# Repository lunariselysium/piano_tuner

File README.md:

# PianoTuner Legacy Prototype

Status:
Archived

This repository contains early prototype implementation
developed during the initial research phase.

Current commercial development has migrated to:
Melspectrum tech organization private repositories.

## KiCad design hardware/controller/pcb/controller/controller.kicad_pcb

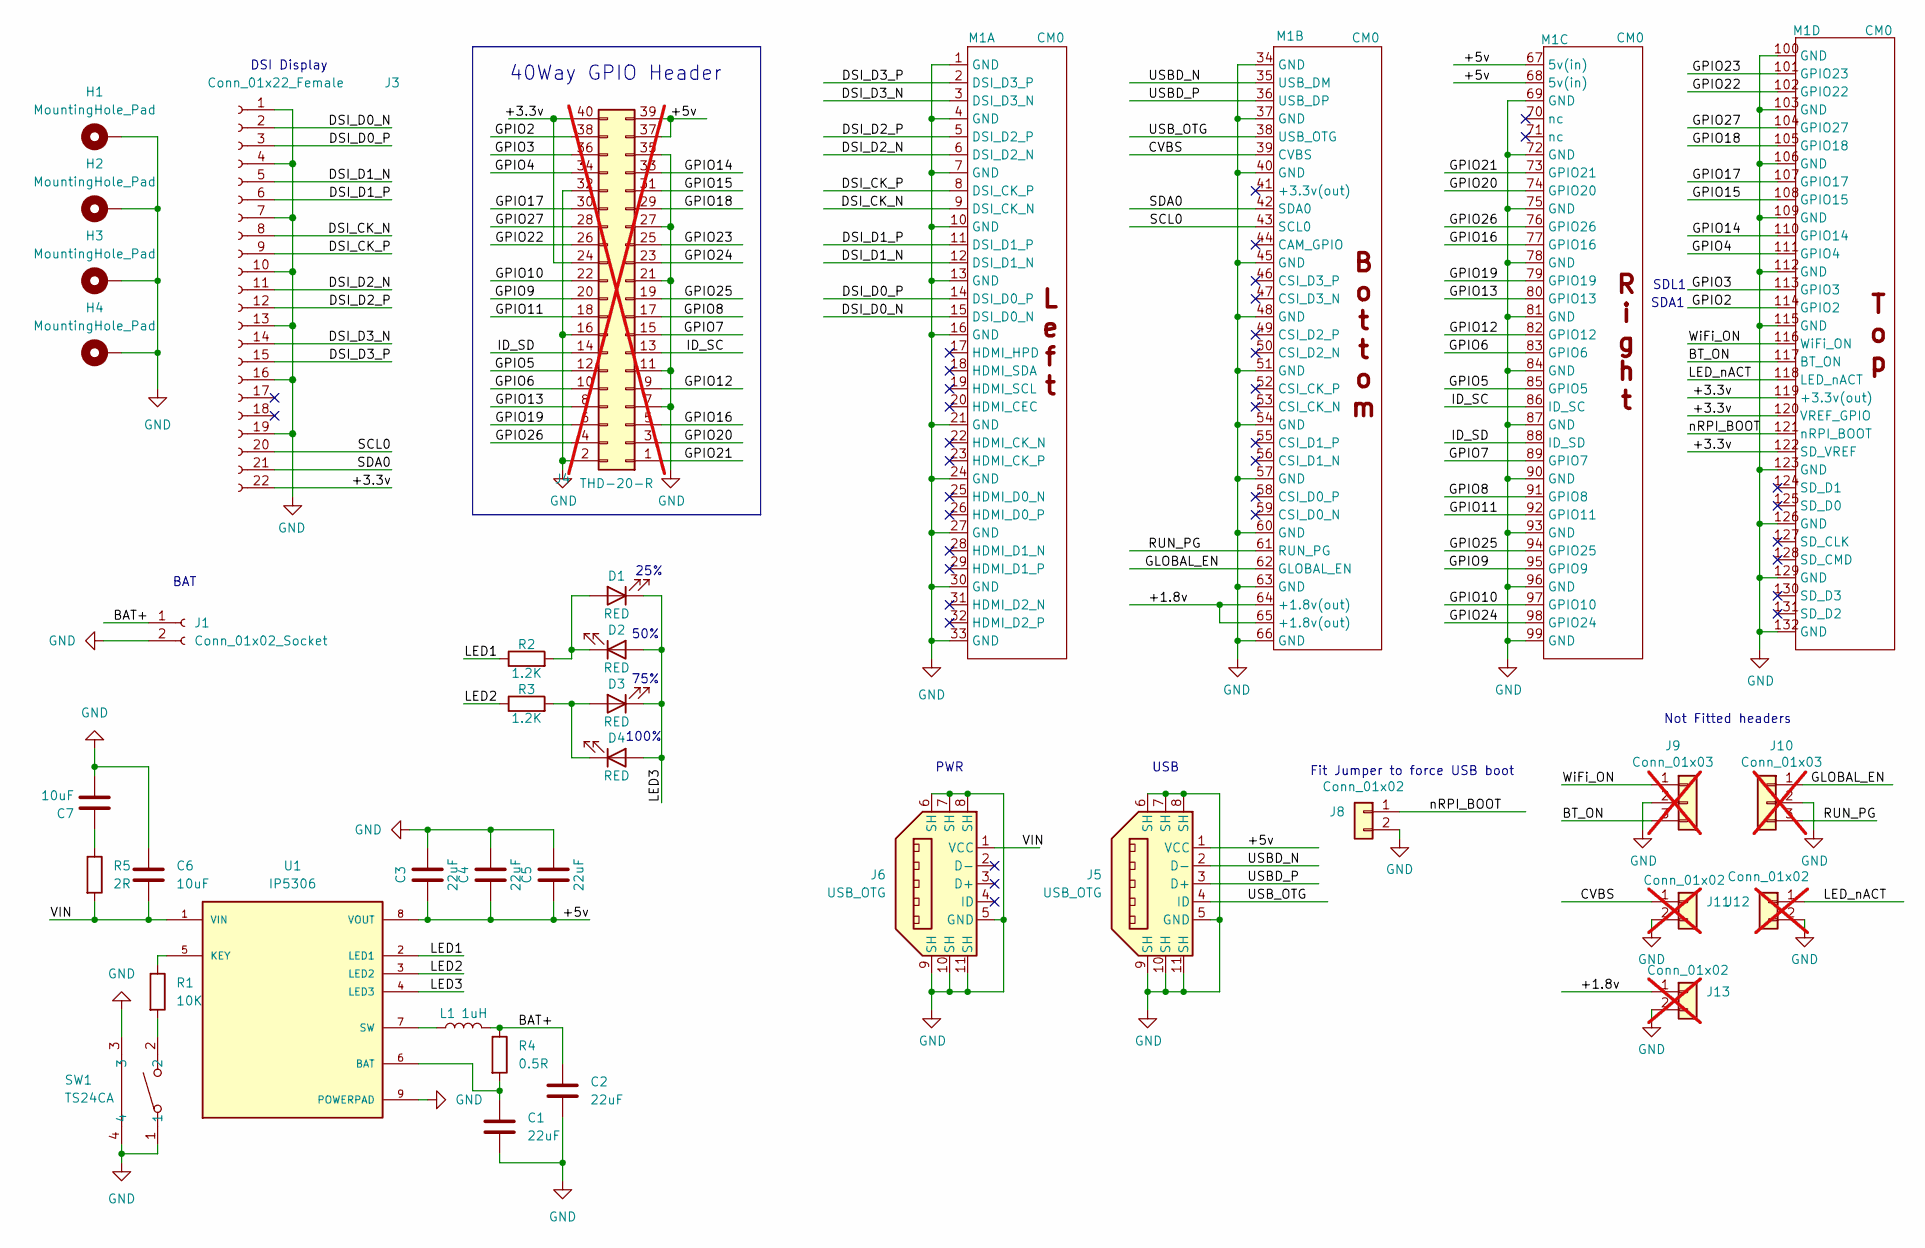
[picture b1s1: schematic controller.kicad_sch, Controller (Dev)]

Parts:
C1, C2, C3, C4, C5: 22uF; C_0201_0603Metric_Pad0.64x0.40mm_HandSolder
C6, C7: 10uF; C_0201_0603Metric_Pad0.64x0.40mm_HandSolder
D1, D2, D3, D4: RED; LED_0201_0603Metric_Pad0.64x0.40mm_HandSolder
H1, H2, H3, H4: MountingHole_Pad; MountingHole_2.7mm_M2.5_Pad
J1: Conn_01x02_Socket; JST_PH_S2B-PH-K_1x02_P2.00mm_Horizontal
J3: Conn_01x22_Female; Hirose_FH12-22S-0.5SH_1x22-1MP_P0.50mm_Horizontal; Part Description 22 Position FFC, FPC Connector Contacts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
J4: THD-20-R; PinHeader_2x20_P1.00mm_Vertical_SMD; Part Description PinHeader_2x20_P2.54mm_Vertical; not fitted
J5, J6: USB_OTG; amphenol_10103594-0001lf; Part Description USB - micro B USB 2.0 Receptacle Connec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
J8: Conn_01x02; PinHeader_1x02_P2.54mm_Vertical
J9, J10: Conn_01x03; PinHeader_1x03_P2.54mm_Vertical; Part Description 3pin 0.1" connector; not fitted
J11, J12, J13: Conn_01x02; PinHeader_1x02_P2.54mm_Vertical; not fitted
L1: 1uH; L_Changjiang_FXL0420
M1: CM0; Part Description Compute Module 0
R1: 10K; R_0201_0603Metric_Pad0.64x0.40mm_HandSolder
R2, R3: 1.2K; R_0201_0603Metric_Pad0.64x0.40mm_HandSolder
R4: 0.5R; R_0201_0603Metric_Pad0.64x0.40mm_HandSolder
R5: 2R; R_0201_0603Metric_Pad0.64x0.40mm_HandSolder
SW1: TS24CA; SW-SMD_2P-TS24CA; LCSC Part C393942
U1: IP5306; SOP127P600X165-9N; PARTREV 1.31

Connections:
/+1.8v: J13.1, M1.64 (+1.8v(out)), M1.65 (+1.8v(out))
/+3.3v: J3.22, J4.24, J4.40, M1.119 (+3.3v(out)), M1.120 (VREF_GPIO), M1.122 (SD_VREF)
/+5v: C3.1, C4.1, C5.1, J4.37, J4.39, J5.1 (VCC), M1.67 (5v(in)), M1.68 (5v(in)), U1.8 (VOUT)
/BAT+: C2.1, J1.1, L1.2, R4.1
/BT_ON: J9.3, M1.117 (BT_ON)
/CVBS: J11.1, M1.39 (CVBS)
/DSI_CK_N: J3.8, M1.9 (DSI_CK_N)
/DSI_CK_P: J3.9, M1.8 (DSI_CK_P)
/DSI_D0_N: J3.2, M1.15 (DSI_D0_N)
/DSI_D0_P: J3.3, M1.14 (DSI_D0_P)
/DSI_D1_N: J3.5, M1.12 (DSI_D1_N)
/DSI_D1_P: J3.6, M1.11 (DSI_D1_P)
/DSI_D2_N: J3.11, M1.6 (DSI_D2_N)
/DSI_D2_P: J3.12, M1.5 (DSI_D2_P)
/DSI_D3_N: J3.14, M1.3 (DSI_D3_N)
/DSI_D3_P: J3.15, M1.2 (DSI_D3_P)
/GLOBAL_EN: J10.1, M1.62 (GLOBAL_EN)
/GPIO2: J4.38, M1.114 (GPIO2)
/GPIO3: J4.36, M1.113 (GPIO3)
/GPIO4: J4.34, M1.111 (GPIO4)
/GPIO5: J4.12, M1.85 (GPIO5)
/GPIO6: J4.10, M1.83 (GPIO6)
/GPIO7: J4.15, M1.89 (GPIO7)
/GPIO8: J4.17, M1.91 (GPIO8)
/GPIO9: J4.20, M1.95 (GPIO9)
/GPIO10: J4.22, M1.97 (GPIO10)
/GPIO11: J4.18, M1.92 (GPIO11)
/GPIO12: J4.9, M1.82 (GPIO12)
/GPIO13: J4.8, M1.80 (GPIO13)
/GPIO14: J4.33, M1.110 (GPIO14)
/GPIO15: J4.31, M1.108 (GPIO15)
/GPIO16: J4.5, M1.77 (GPIO16)
/GPIO17: J4.30, M1.107 (GPIO17)
/GPIO18: J4.29, M1.105 (GPIO18)
/GPIO19: J4.6, M1.79 (GPIO19)
/GPIO20: J4.3, M1.74 (GPIO20)
/GPIO21: J4.1, M1.73 (GPIO21)
/GPIO22: J4.26, M1.102 (GPIO22)
/GPIO23: J4.25, M1.101 (GPIO23)
/GPIO24: J4.23, M1.98 (GPIO24)
/GPIO25: J4.19, M1.94 (GPIO25)
/GPIO26: J4.4, M1.76 (GPIO26)
/GPIO27: J4.28, M1.104 (GPIO27)
/ID_SC: J4.13, M1.86 (ID_SC)
/ID_SD: J4.14, M1.88 (ID_SD)
/LED1: R2.1, U1.2 (LED1)
/LED2: R3.1, U1.3 (LED2)
/LED3: D1.1 (K), D2.2 (A), D3.1 (K), D4.2 (A), U1.4 (LED3)
/LED_nACT: J12.1, M1.118 (LED_nACT)
/RUN_PG: J10.3, M1.61 (RUN_PG)
/SCL0: J3.20, M1.43 (SCL0)
/SDA0: J3.21, M1.42 (SDA0)
/USBD_N: J5.2 (D-), M1.35 (USB_DM)
/USBD_P: J5.3 (D+), M1.36 (USB_DP)
/USB_OTG: J5.4 (ID), M1.38 (USB_OTG)
/VIN: C6.2, J6.1 (VCC), R5.2, U1.1 (VIN)
/WiFi_ON: J9.1, M1.116 (WiFi_ON)
/nRPI_BOOT: J8.1, M1.121 (nRPI_BOOT)
GND: C1.2, C2.2, C3.2, C4.2, C5.2, C6.1, C7.1, H1.1, H2.1, H3.1, H4.1, J1.2, J3.1, J3.4, J3.7, J3.10, J3.13, J3.16, J3.19, J4.2, J4.7, J4.11, J4.16, J4.21, J4.27, J4.32, J4.35, J5.5 (GND), J5.6 (SH), J5.7 (SH), J5.8 (SH), J5.9 (SH), J5.10 (SH), J5.11 (SH), J6.5 (GND), J6.6 (SH), J6.7 (SH), J6.8 (SH), J6.9 (SH), J6.10 (SH), J6.11 (SH), J8.2, J9.2, J10.2, J11.2, J12.2, J13.2, M1.1 (GND), M1.4 (GND), M1.7 (GND), M1.10 (GND), M1.13 (GND), M1.16 (GND), M1.21 (GND), M1.24 (GND), M1.27 (GND), M1.30 (GND), M1.33 (GND), M1.34 (GND), M1.37 (GND), M1.40 (GND), M1.45 (GND), M1.48 (GND), M1.51 (GND), M1.54 (GND), M1.57 (GND), M1.60 (GND), M1.63 (GND), M1.66 (GND), M1.69 (GND), M1.72 (GND), M1.75 (GND), M1.78 (GND), M1.81 (GND), M1.84 (GND), M1.87 (GND), M1.90 (GND), M1.93 (GND), M1.96 (GND), M1.99 (GND), M1.100 (GND), M1.103 (GND), M1.106 (GND), M1.109 (GND), M1.112 (GND), M1.115 (GND), M1.123 (GND), M1.126 (GND), M1.129 (GND), M1.132 (GND), SW1.1, SW1.3, SW1.4, U1.9 (POWERPAD)
unnamed: C7.2, R5.1
unnamed: D1.2 (A), D2.1 (K), R2.2
unnamed: D3.2 (A), D4.1 (K), R3.2
unnamed: R1.2, SW1.2
unnamed: C1.1, R4.2, U1.6 (BAT)
unnamed: R1.1, U1.5 (KEY)
unnamed: L1.1, U1.7 (SW)

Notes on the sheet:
100%
SDL1
Fit Jumper to force USB boot
Not Fitted headers
DSI Display
SDA1
40Way GPIO Header
25%
50%
75%
USB
BAT
PWR

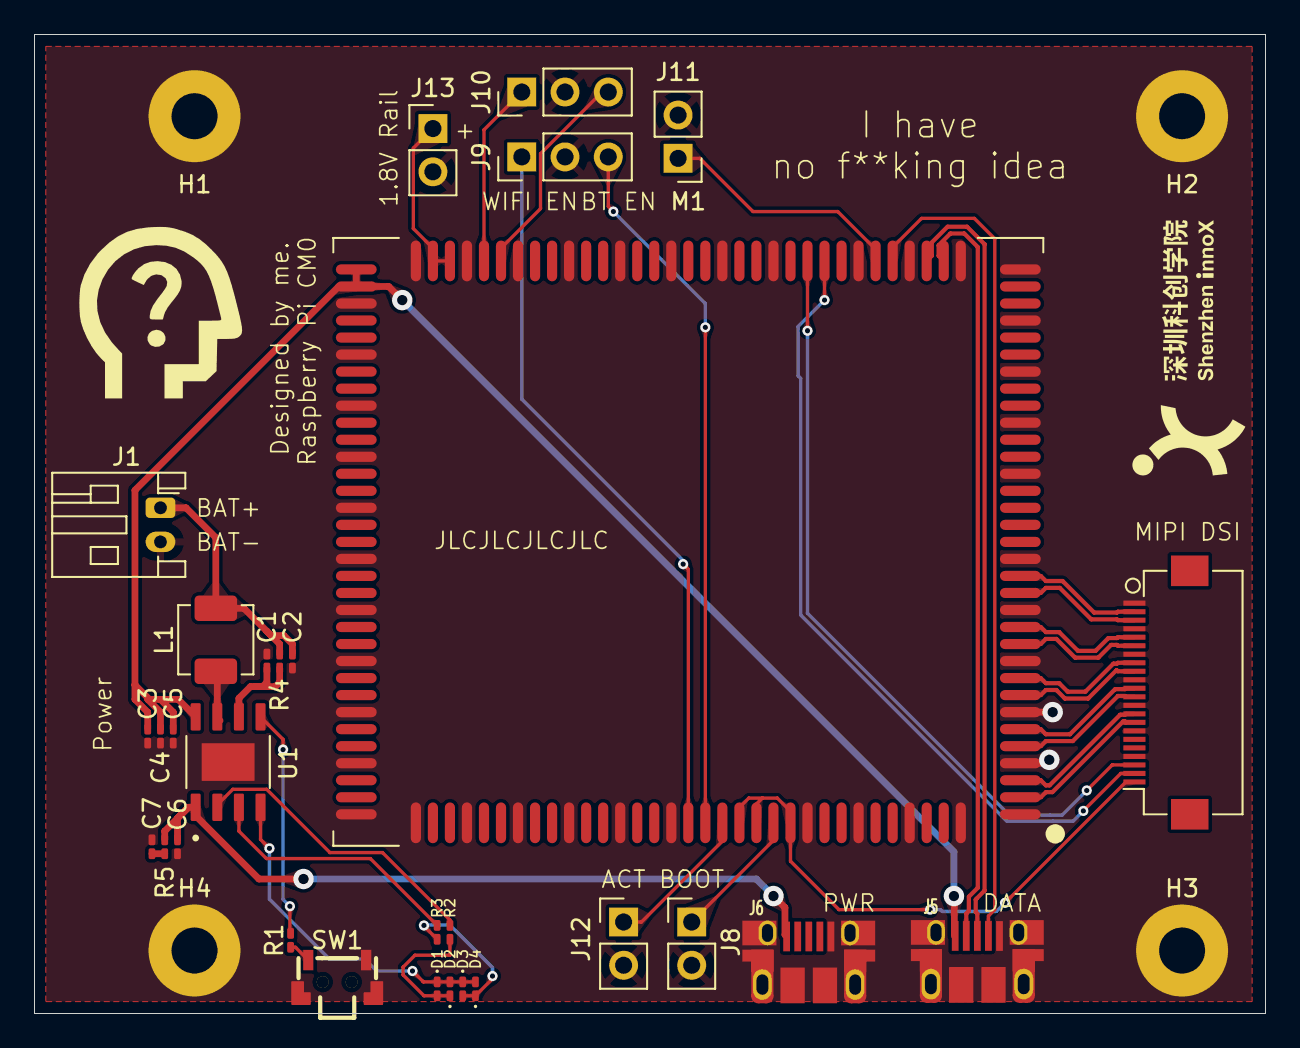
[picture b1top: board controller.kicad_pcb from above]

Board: 2 copper layers, 72.3 x 57.5 mm, 34 parts (0 on the bottom side), 38 nets.

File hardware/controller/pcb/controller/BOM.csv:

Id;Designator;Footprint;Quantity;Designation;Supplier and ref
1;J6,J5;amphenol_10103594-0001lf;2;USB_OTG;szlcsc
2;D4,D2,D3,D1;LED_0201_0603Metric_Pad0.64x0.40mm_HandSolder;4;RED;szlcsc
3;C1,C5,C2,C4,C3;C_0201_0603Metric_Pad0.64x0.40mm_HandSolder;5;22uF;szlcsc
4;R4;R_0201_0603Metric_Pad0.64x0.40mm_HandSolder;1;0.5R;szlcsc
5;M1;CM0;1;CM0;tb
6;R2,R3;R_0201_0603Metric_Pad0.64x0.40mm_HandSolder;2;1.2K;szlcsc
7;U1;SOP127P600X165-9N;1;IP5306;szlcsc
8;J1;JST_PH_S2B-PH-K_1x02_P2.00mm_Horizontal;1;Conn_01x02_Socket;szlcsc
9;J3;Hirose_FH12-22S-0.5SH_1x22-1MP_P0.50mm_Horizontal;1;Conn_01x22_Female;tb
10;C7,C6;C_0201_0603Metric_Pad0.64x0.40mm_HandSolder;2;10uF;szlcsc
11;R5;R_0201_0603Metric_Pad0.64x0.40mm_HandSolder;1;2R;szlcsc
12;L1;L_Changjiang_FXL0420;1;1uH;szlcsc
13;J8;PinHeader_1x02_P2.54mm_Vertical;1;Conn_01x02;szlcsc
14;SW1;SW-SMD_2P-TS24CA;1;TS24CA;szlcsc
15;R1;R_0201_0603Metric_Pad0.64x0.40mm_HandSolder;1;10K;szlcsc

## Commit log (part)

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2025-12-13 forgot to commmit
2025-12-13 Add inharmonicity analysis and Kivy GUI example
    Added inharmonicity_calc.py for piano note analysis and inharmonicity coefficient calculation. Refactored mic_tester.py to use sounddevice for audio input and simplified the code. Introduced hello_wo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
2025-12-13 Add initial app modules for piano tuner UI and logic
    Introduces the main Kivy app structure with multiple screens, including connection, calibration, measurement, calculation, and tuning. Adds supporting modules for configuration, audio hardware intera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
2025-12-20 Refactor audio analysis and improve calibration UI
    Refactored color constants in config.py for consistency. Enhanced hardware.py with improved audio analysis, including partials and inharmonicity calculation, and added debouncing logic. Updated main.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
2025-12-20 Improve audio analysis with HPS and better partial detection
    Replaces basic FFT peak detection with Harmonic Product Spectrum (HPS) for more robust fundamental frequency estimation. Adds parabolic interpolation for peak precision, refines partials search, and 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
2025-12-20 Add multi-sample capture and silence check to measurement
    Implemented a buffer to collect 5 samples per note, requiring 0.5s of silence between samples to prevent rapid input. The average (excluding min and max) is stored for each note, improving measuremen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
2025-12-20 Improve silence detection logic in MeasurementScreen
    Adjusted the silence threshold to 90% of sensitivity to prevent getting stuck when the noise floor is close to the sensitivity value. Enhanced status label feedback for users, discarded stray analysi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
2025-12-20 Implement interval generation and optimize tuning calculation
    Added intervals.py to generate musical intervals for tuning optimization. Refactored calculation.py to use the new interval generation, improved multiprocessing logic, and implemented a Numba-optimiz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
2025-12-20 Add BLE device scanning and async connection logic
    Refactored TunerDevice to support real BLE device scanning and connection using Bleak, with a mock device for debugging. Updated ConnectionScreen to asynchronously scan for devices, update the UI wit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
2025-12-23 Improve audio check interval and needle position handling
    Reduced the audio check interval from 0.1s to 0.05s for more responsive updates. Refactored needle position calculation to ensure the value is a standard float, improving compatibility with Kivy.
2025-12-23 Add measurement configuration screen and logic
    Introduces a new MeasurementConfigScreen to allow users to select note patterns and sample count before measurement. Updates the app logic to use these settings during measurement, and adjusts screen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
2025-12-23 Refactor measurement to handle multiple strings per note
    Updated MeasurementScreen to support measuring and storing inharmonicity for each string (left, center, right) per note, with UI and logic for string selection and skipping. Added StringVisualizer wi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
2025-12-25 Pianotuner_for_Esp32_s3_TMC2209
2026-02-11 Added documentation
2026-02-11 Add tuning presets UI and pass custom weights
    Introduce selectable tuning presets and custom weight sliders, and thread chosen weights into the optimization pipeline. Added TUNING_PRESETS in intervals.py and a new TuningPresetScreen (Python + KV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
